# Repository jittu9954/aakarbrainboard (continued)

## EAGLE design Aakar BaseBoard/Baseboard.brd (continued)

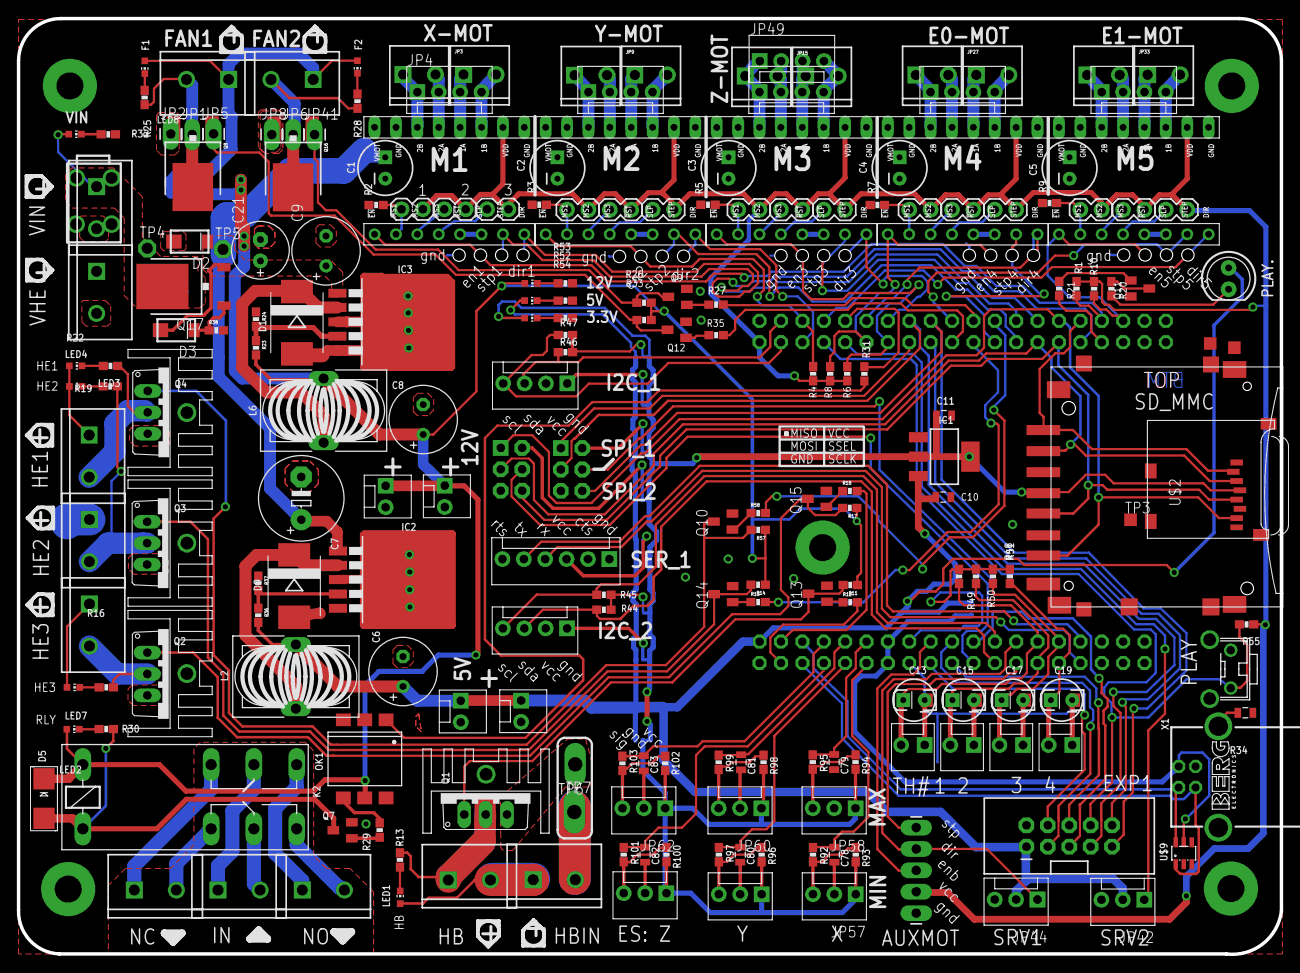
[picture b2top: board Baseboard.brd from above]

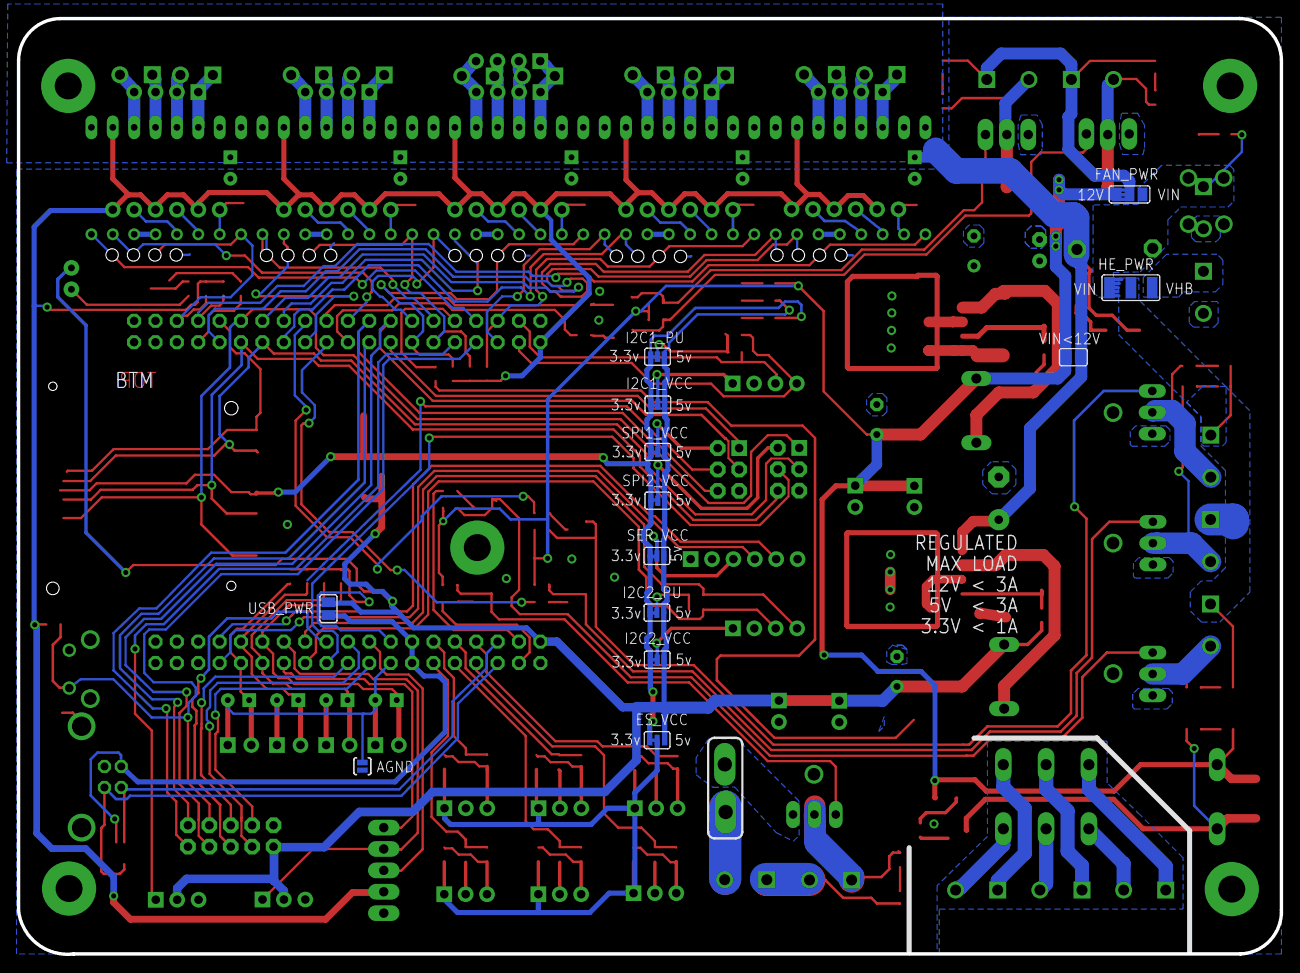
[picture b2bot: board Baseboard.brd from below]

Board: 2 copper layers, 150.0 x 111.1 mm, 246 parts (13 on the bottom side), 176 nets.

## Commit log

2015-03-23 Aakar Brainboard initial commit
2015-03-23 Readme created
